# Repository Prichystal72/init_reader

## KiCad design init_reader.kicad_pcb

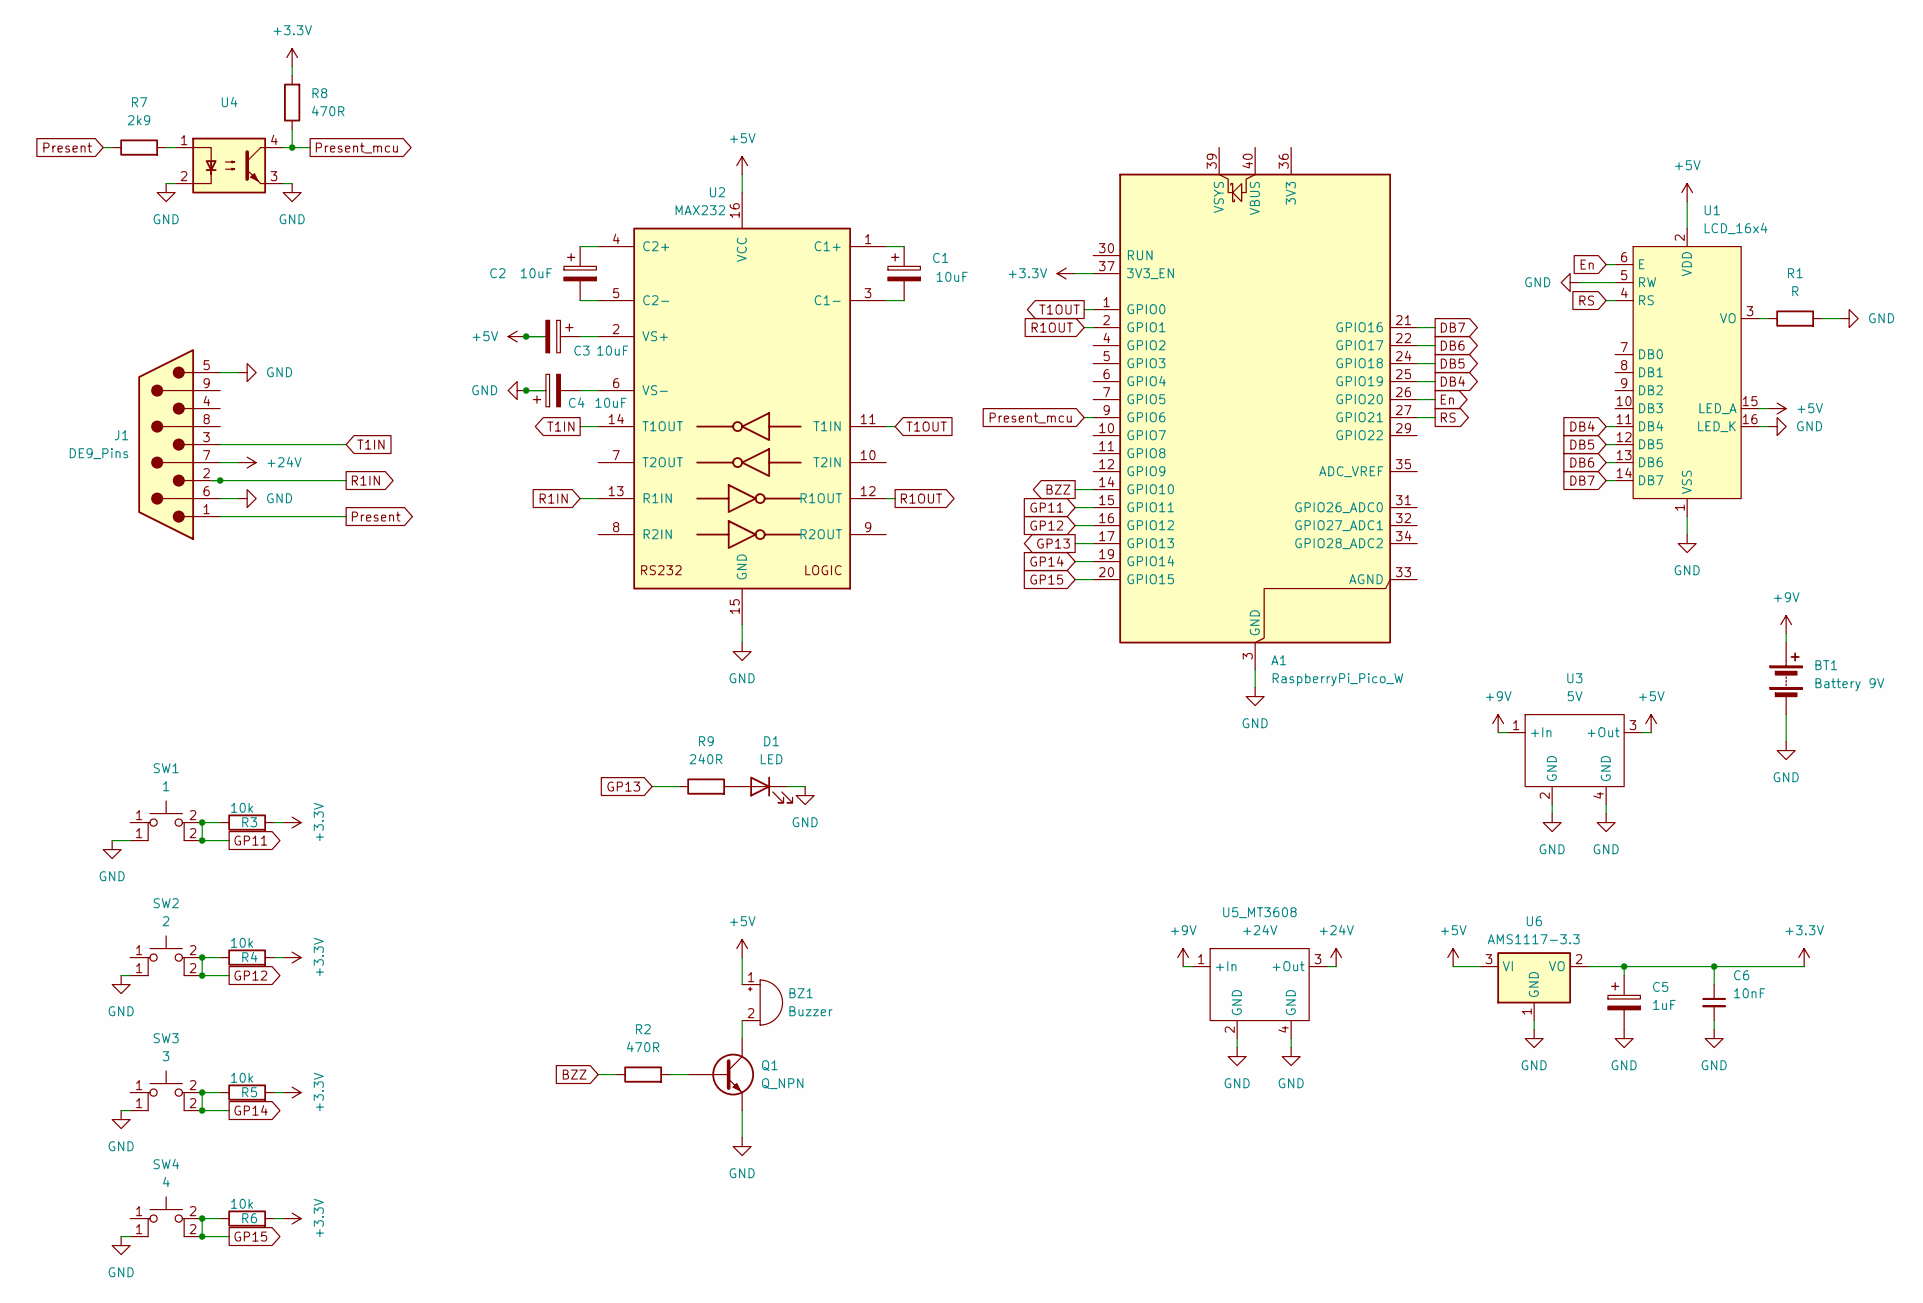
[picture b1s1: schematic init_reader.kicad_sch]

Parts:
A1: RaspberryPi_Pico_W; RaspberryPi_Pico_Common_THT
BT1: Battery 9V; BatteryHolder_MPD_BA9VPC_1xPP3
BZ1: Buzzer; Buzzer_12x9.5RM7.6
C1, C2, C3, C4: 10uF; CP_Radial_D5.0mm_P2.50mm
C5: 1uF; CP_Radial_D5.0mm_P2.50mm
C6: 10nF; C_0603_1608Metric; Voltage 1kV; Tolerance 100%
D1: LED; LED_D3.0mm
J1: DE9_Pins; DSUB-9_Pins_Horizontal_P2.77x2.54mm_EdgePinOffset9.40mm
Q1: Q_NPN; TO-92_Inline
R1: R; R_Axial_DIN0207_L6.3mm_D2.5mm_P7.62mm_Horizontal
R2, R8: 470R; R_Axial_DIN0207_L6.3mm_D2.5mm_P7.62mm_Horizontal
R3, R4, R5, R6: 10k; R_Axial_DIN0207_L6.3mm_D2.5mm_P7.62mm_Horizontal
R7: 2k9; R_Axial_DIN0207_L6.3mm_D2.5mm_P7.62mm_Horizontal
R9: 240R; R_Axial_DIN0207_L6.3mm_D2.5mm_P7.62mm_Horizontal
SW1: 1; SW_TH_Tactile_Omron_B3F-100x
SW2: 2; SW_TH_Tactile_Omron_B3F-100x
SW3: 3; SW_TH_Tactile_Omron_B3F-100x
SW4: 4; SW_TH_Tactile_Omron_B3F-100x
U1: LCD_16x4; AC-164A
U2: MAX232; DIP-16_W7.62mm
U3: 5V; dc-dc-HW613
U4: Optocoupler_DC_PhotoNPN_AKEC; DIP-4_W7.62mm
U5_MT3608: +24V; dc_dc_MT3608
U6: AMS1117-3.3; SOT-223-3_TabPin2

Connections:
+3.3V: A1.37 (3V3_EN), C5.1, C6.1, R3.2, R4.2, R5.2, R6.2, R8.2, U6.2 (VO)
+5V: BZ1.1 (+), C3.2, U1.2 (VDD), U1.15 (LED_A), U2.16 (VCC), U3.3 (+Out), U6.3 (VI)
+9V: BT1.1 (+), U3.1 (+In), U5_MT3608.1 (+In)
+24V: J1.7, U5_MT3608.3 (+Out)
BZZ: A1.14 (GPIO10), R2.1
DB4: A1.25 (GPIO19), U1.11 (DB4)
DB5: A1.24 (GPIO18), U1.12 (DB5)
DB6: A1.22 (GPIO17), U1.13 (DB6)
DB7: A1.21 (GPIO16), U1.14 (DB7)
En: A1.26 (GPIO20), U1.6 (E)
GND: A1.3 (GND), A1.8 (GND), A1.13 (GND), A1.18 (GND), A1.23 (GND), A1.28 (GND), A1.38 (GND), BT1.2 (-), C4.1, C5.2, C6.2, D1.1 (K), J1.5, J1.6, Q1.3 (E), R1.2, SW1.1, SW2.1, SW3.1, SW4.1, U1.1 (VSS), U1.5 (RW), U1.16 (LED_K), U2.15 (GND), U3.2 (GND), U3.4 (GND), U4.2, U4.3, U5_MT3608.2 (GND), U5_MT3608.4 (GND), U6.1 (GND)
GP11: A1.15 (GPIO11), R3.1, SW1.2
GP12: A1.16 (GPIO12), R4.1, SW2.2
GP13: A1.17 (GPIO13), R9.1
GP14: A1.19 (GPIO14), R5.1, SW3.2
GP15: A1.20 (GPIO15), R6.1, SW4.2
unnamed: BZ1.2 (-), Q1.1 (C)
unnamed: D1.2 (A), R9.2
unnamed: Q1.2 (B), R2.2
unnamed: R7.2, U4.1
unnamed: R1.1, U1.3 (VO)
unnamed: C1.1, U2.1 (C1+)
unnamed: C1.2, U2.3 (C1-)
unnamed: C2.1, U2.4 (C2+)
unnamed: C2.2, U2.5 (C2-)
unnamed: C3.1, U2.2 (VS+)
unnamed: C4.2, U2.6 (VS-)
Present: J1.1, R7.1
Present_mcu: A1.9 (GPIO6), R8.1, U4.4
R1IN: J1.2, U2.13 (R1IN)
R1OUT: A1.2 (GPIO1), U2.12 (R1OUT)
RS: A1.27 (GPIO21), U1.4 (RS)
T1IN: J1.3, U2.14 (T1OUT)
T1OUT: A1.1 (GPIO0), U2.11 (T1IN)

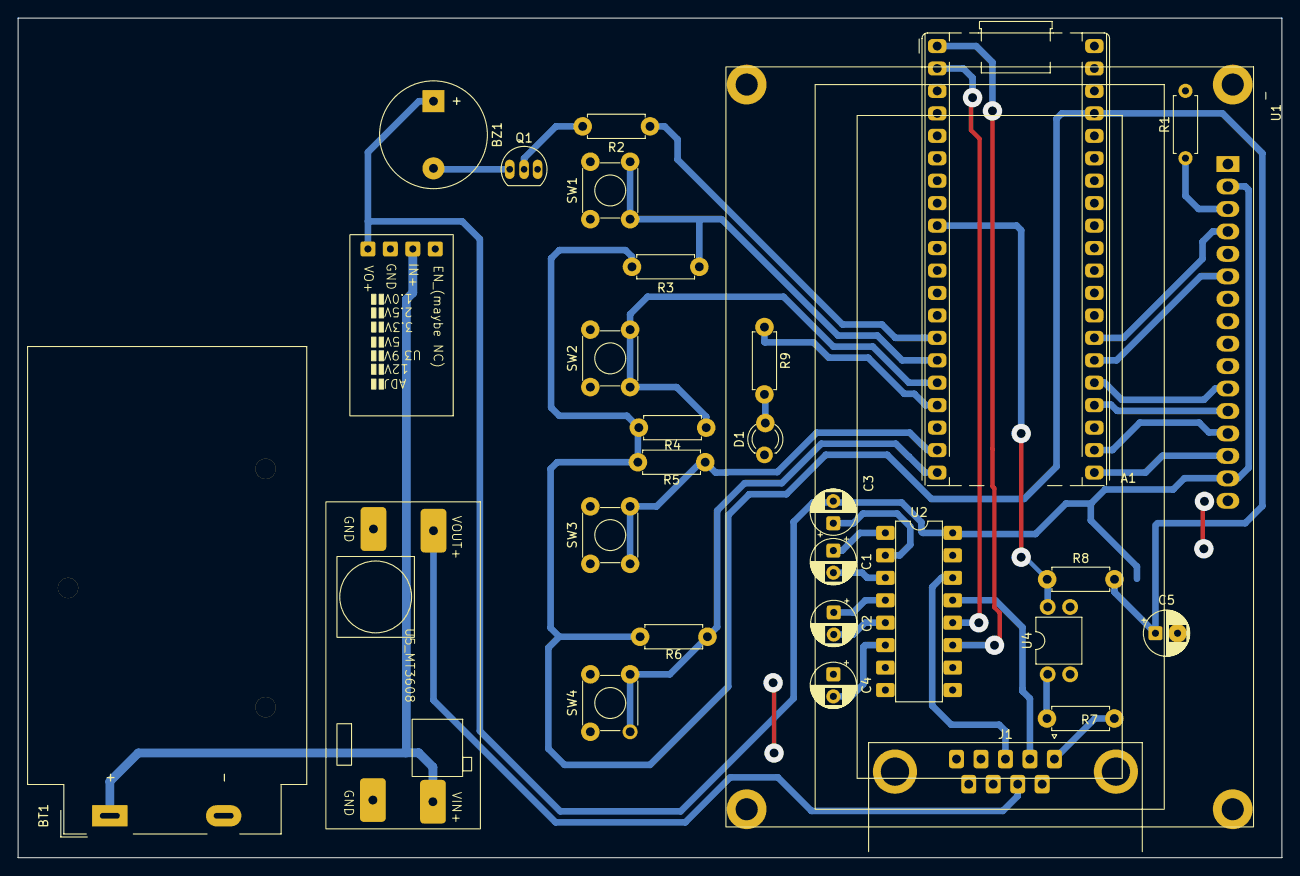
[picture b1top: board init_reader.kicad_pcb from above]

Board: 2 copper layers, 143.0 x 95.0 mm, 30 parts (1 on the bottom side), 34 nets.

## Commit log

2026-02-04 init commit
2026-02-05 add datasheet
2026-02-06 update schematics
2026-02-24 add all components - basic circuit
2026-02-27 update all
2026-03-01 change footprint dsub9 + create cnc folder&files
2026-03-02 thick-up all routes and pads
